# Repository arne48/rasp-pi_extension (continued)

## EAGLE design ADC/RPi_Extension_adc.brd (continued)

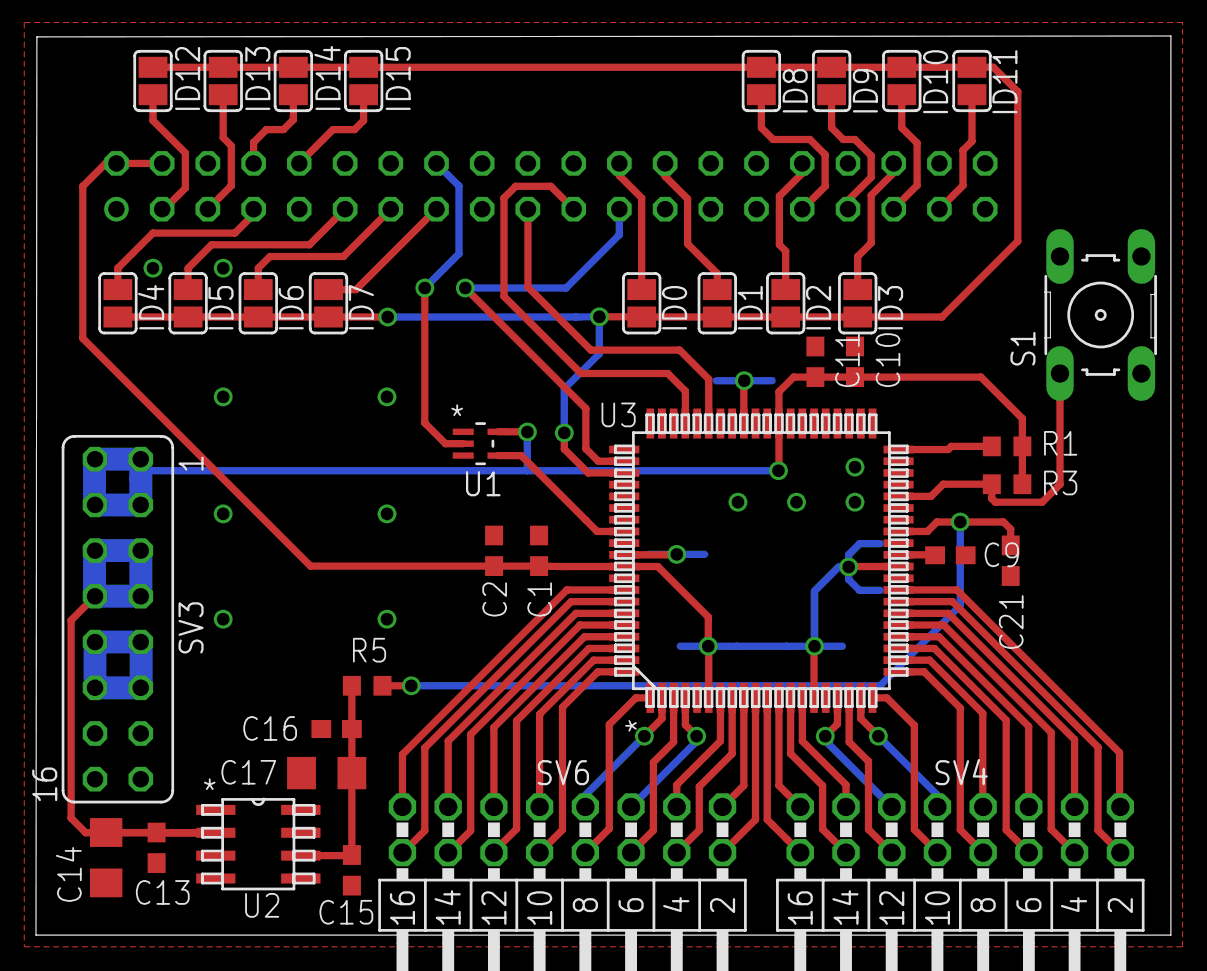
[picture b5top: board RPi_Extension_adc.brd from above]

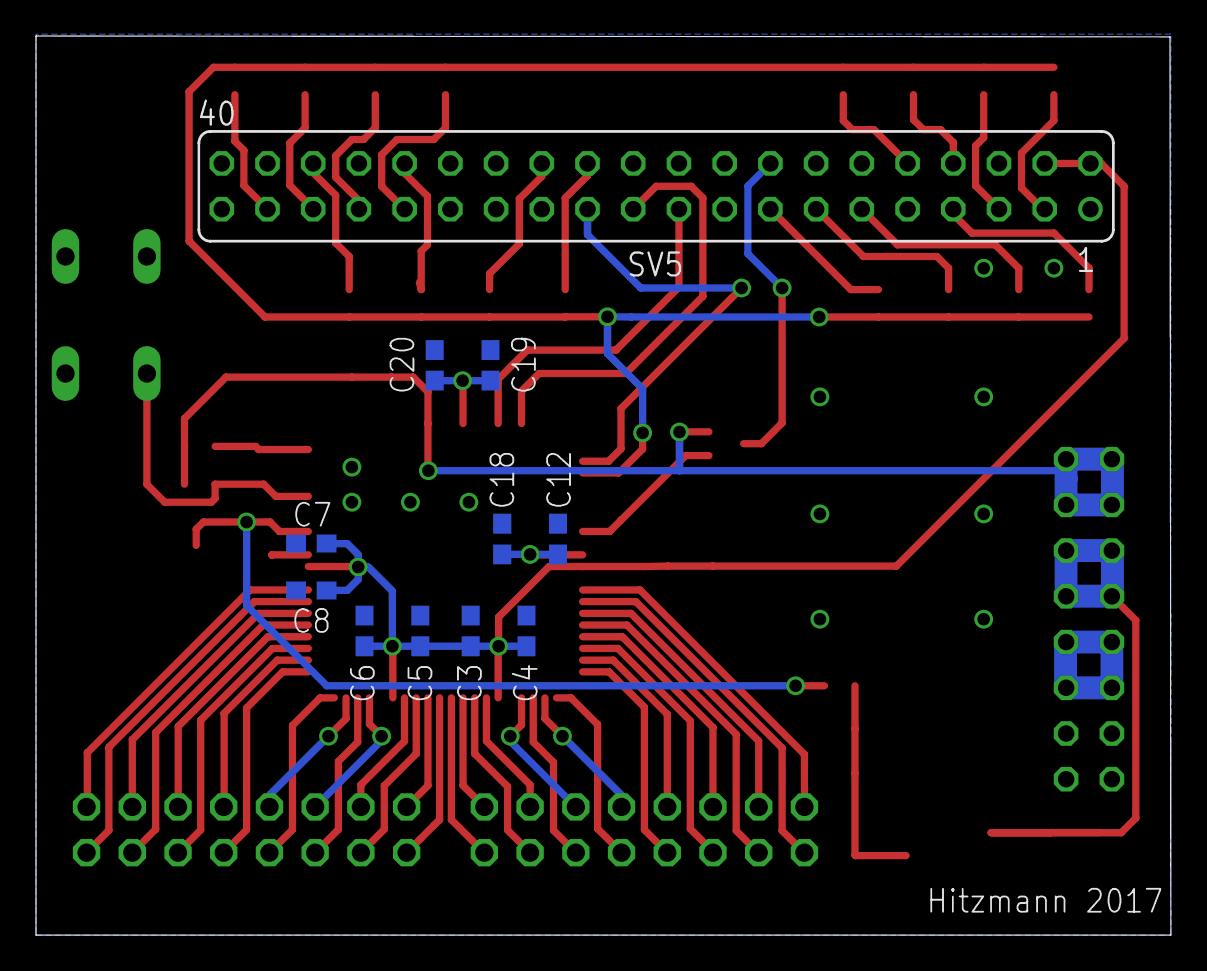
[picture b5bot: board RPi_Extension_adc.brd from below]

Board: 2 copper layers, 63.0 x 50.0 mm, 48 parts (11 on the bottom side), 66 nets.

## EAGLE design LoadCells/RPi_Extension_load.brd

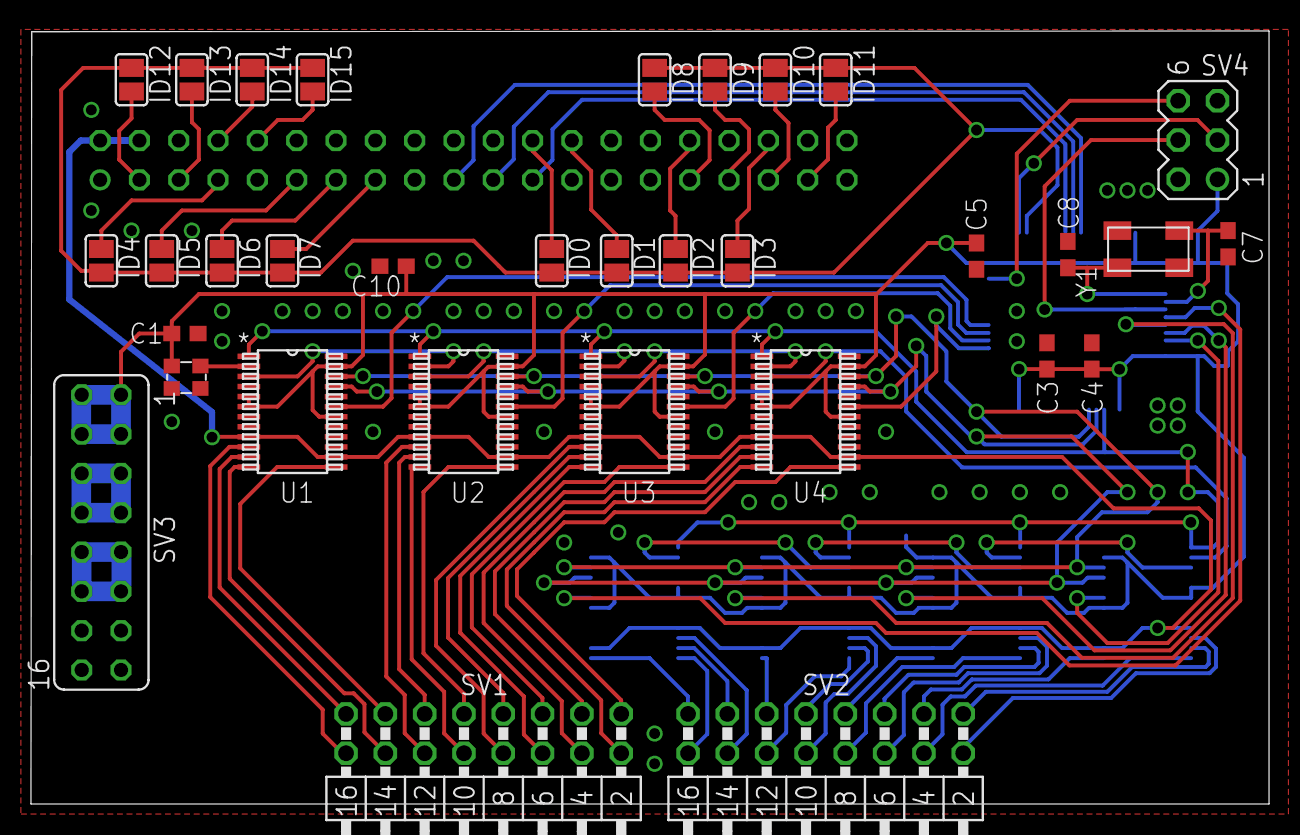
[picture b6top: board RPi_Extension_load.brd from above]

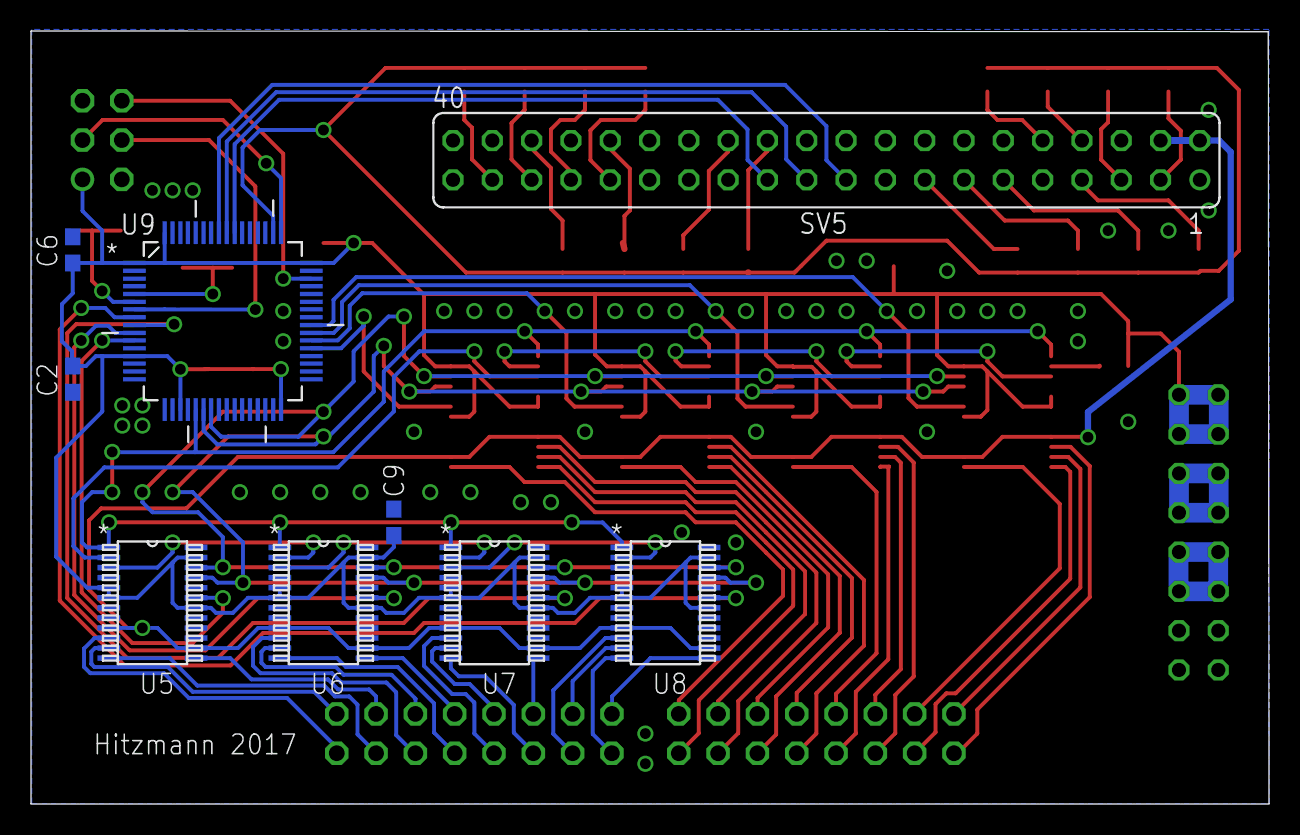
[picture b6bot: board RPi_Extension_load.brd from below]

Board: 2 copper layers, 80.0 x 50.0 mm, 42 parts (9 on the bottom side), 81 nets.

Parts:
C1, C2, C3, C4, C5, C6, C9, C10: 100nF; C0603
C7, C8: 33pf; C0603
ID0, ID1, ID2, ID3, ID4, ID5, ID6, ID7, ID8, ID9, ID10, ID11, ID12, ID13, ID14, ID15: SJ
SV1, SV2: MA08-2W
SV3: FE08-2
SV4: MA03-2
SV5: FE20-2
U1, U2, U3, U4, U5, U6, U7, U8: AD7730BRUZ; RU_24
U9: STM32F103RCT6; QFP50P1200X1200X160-64N
Y1: ABM3B
Y2: KC2520B-C1

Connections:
+5V: SV5.2, SV5.4, U1.9, U1.14, U2.9, U2.14, U3.9, U3.14, U4.9, U4.14, U5.9, U5.14, U6.9, U6.14, U7.9, U7.14, U8.9, U8.14
DVCC: C1.2, C2.2, C3.1, C4.1, C5.1, C6.1, C9.1, C10.1, SV3.1, SV3.2, SV3.3, SV3.4, SV4.1, U1.5, U1.6, U1.18, U1.23, U2.5, U2.6, U2.18, U2.23, U3.5, U3.6, U3.18, U3.23, U4.5, U4.6, U4.18, U4.23, U5.5, U5.6, U5.18, U5.23, U6.5, U6.6, U6.18, U6.23, U7.5, U7.6, U7.18, U7.23, U8.5, U8.6, U8.18, U8.23, U9.1, U9.13, U9.19, U9.32, U9.48, U9.64, Y2.4
GND: C1.1, C2.1, C3.2, C4.2, C5.2, C6.2, C7.2, C8.2, C9.2, C10.2, SV3.13, SV3.14, SV3.15, SV3.16, SV4.2, SV4.5, SV5.6, SV5.9, SV5.14, SV5.20, SV5.25, SV5.30, SV5.34, SV5.39, U1.4, U1.8, U1.15, U1.24, U2.4, U2.8, U2.15, U2.24, U3.4, U3.8, U3.15, U3.24, U4.4, U4.8, U4.15, U4.24, U5.4, U5.8, U5.15, U5.24, U6.4, U6.8, U6.15, U6.24, U7.4, U7.8, U7.15, U7.24, U8.4, U8.8, U8.15, U8.24, U9.12, U9.18, U9.31, U9.47, U9.63, Y1.2, Y1.4, Y2.2
MCLK: U1.2, Y2.3
MISO: SV5.21, U9.56
MOSI: SV5.19, U9.57
unnamed: ID11.1, SV5.37
unnamed: C8.1, U9.5, Y1.1
unnamed: C7.1, U9.6, Y1.3
unnamed: ID10.1, SV5.35
unnamed: ID9.1, SV5.33
unnamed: ID8.1, SV5.31
unnamed: ID14.1, SV5.8
unnamed: ID15.1, SV5.10
unnamed: ID12.1, SV5.3
unnamed: ID13.1, SV5.5
unnamed: ID3.1, SV5.36
unnamed: ID4.1, SV5.7
unnamed: ID2.1, SV5.32
unnamed: ID1.1, SV5.26
unnamed: ID0.1, SV5.24
unnamed: ID5.1, SV5.11
unnamed: ID6.1, SV5.13
unnamed: ID7.1, SV5.15
NRST: SV4.4, U9.7
SCLK: SV5.23, U9.55
SPI1_MISO: U1.21, U2.21, U3.21, U4.21, U5.21, U6.21, U7.21, U8.21, U9.22
SPI1_MOSI: U1.22, U2.22, U3.22, U4.22, U5.22, U6.22, U7.22, U8.22, U9.23
SPI1_SCK: U1.1, U2.1, U3.1, U4.1, U5.1, U6.1, U7.1, U8.1, U9.21
SS1: U1.19, U9.40
SS2: U2.19, U9.39
SS3: U3.19, U9.38
SS4: U4.19, U9.37
SS5: U5.19, U9.11
SS6: U6.19, U9.10
SS7: U7.19, U9.9
SS8: U8.19, U9.8
SS_STACK: ID0.2, ID1.2, ID2.2, ID3.2, ID4.2, ID5.2, ID6.2, ID7.2, ID8.2, ID9.2, ID10.2, ID11.2, ID12.2, ID13.2, ID14.2, ID15.2, U9.50
SWDCLK: SV4.3, U9.49
SWDIO: SV4.6, U9.46
U1_AIN1_+: SV1.16, U1.10
U1_AIN1_-: SV1.15, U1.11
U1_AIN2_+: SV1.14, U1.12
U1_AIN2_-: SV1.13, U1.13
U1_MCLK_OUT: U1.3, U2.2
U2_AIN1_+: SV1.12, U2.10
U2_AIN1_-: SV1.11, U2.11
U2_AIN2_+: SV1.10, U2.12
U2_AIN2_-: SV1.9, U2.13
U2_MCLK_OUT: U2.3, U3.2
U3_AIN1_+: SV1.8, U3.10
U3_AIN1_-: SV1.7, U3.11
U3_AIN2_+: SV1.6, U3.12
U3_AIN2_-: SV1.5, U3.13
U3_MCLK_OUT: U3.3, U4.2
U4_AIN1_+: SV1.4, U4.10
U4_AIN1_-: SV1.3, U4.11
U4_AIN2_+: SV1.2, U4.12
U4_AIN2_-: SV1.1, U4.13
U4_MCLK_OUT: U4.3, U5.2
U5_AIN1_+: SV2.2, U5.10
U5_AIN1_-: SV2.1, U5.11
U5_AIN2_+: SV2.4, U5.12
U5_AIN2_-: SV2.3, U5.13
U5_MCLK_OUT: U5.3, U6.2
U6_AIN1_+: SV2.6, U6.10
U6_AIN1_-: SV2.5, U6.11
U6_AIN2_+: SV2.8, U6.12
U6_AIN2_-: SV2.7, U6.13
U6_MCLK_OUT: U6.3, U7.2
U7_AIN1_+: SV2.10, U7.10
U7_AIN1_-: SV2.9, U7.11
U7_AIN2_+: SV2.12, U7.12
U7_AIN2_-: SV2.11, U7.13
U7_MCLK_OUT: U7.3, U8.2
U8_AIN1_+: SV2.14, U8.10
U8_AIN1_-: SV2.13, U8.11
U8_AIN2_+: SV2.16, U8.12
U8_AIN2_-: SV2.15, U8.13
VDD: SV3.5, SV3.6, SV3.7, SV3.8
VSS: SV3.9, SV3.10, SV3.11, SV3.12

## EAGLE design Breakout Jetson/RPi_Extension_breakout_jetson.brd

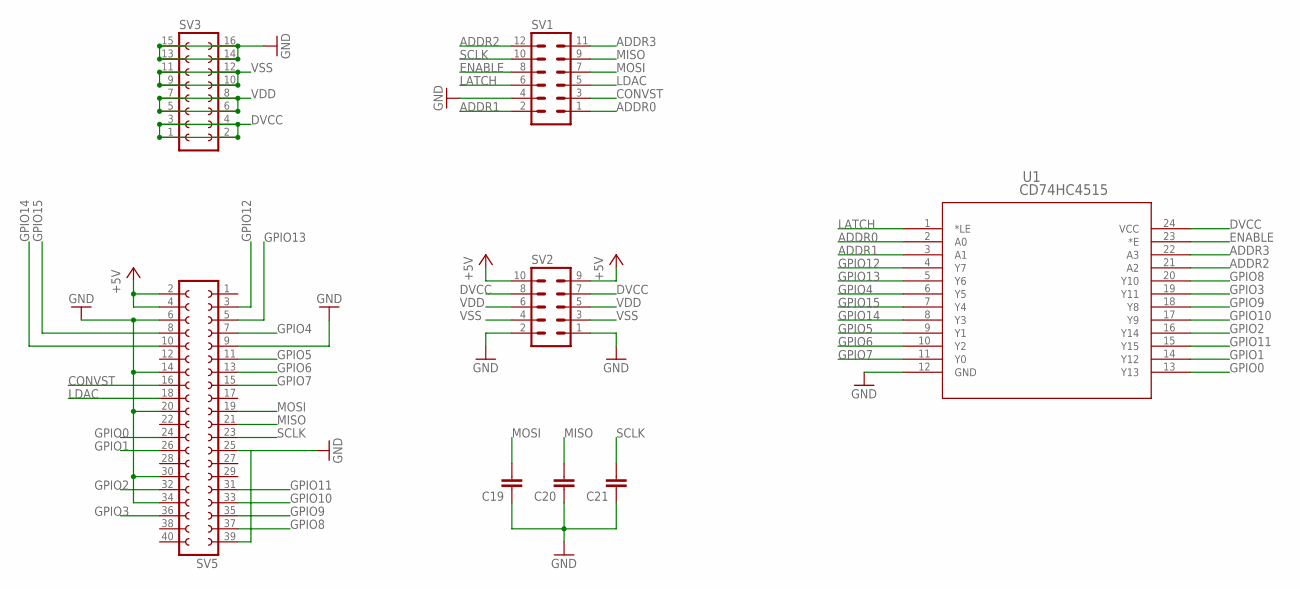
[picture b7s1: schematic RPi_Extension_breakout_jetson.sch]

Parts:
C19, C20, C21: C-EUC0603; C0603
SV1: MA06-2
SV2: MA05-2
SV3: FE08-2
SV5: FE20-2
U1: CD74HC4515; DW24

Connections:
+5V: SV2.9, SV2.10, SV5.2, SV5.4
ADDR0: SV1.1, U1.2 (A0)
ADDR1: SV1.2, U1.3 (A1)
ADDR2: SV1.12, U1.21 (A2)
ADDR3: SV1.11, U1.22 (A3)
CONVST: SV1.3, SV5.16
DVCC: SV2.7, SV2.8, SV3.1, SV3.2, SV3.3, SV3.4, U1.24 (VCC)
ENABLE: SV1.8, U1.23 (*E)
GND: C19.1, C20.1, C21.1, SV1.4, SV2.1, SV2.2, SV3.13, SV3.14, SV3.15, SV3.16, SV5.6, SV5.9, SV5.14, SV5.20, SV5.25, SV5.30, SV5.34, SV5.39, U1.12 (GND)
GPIO0: SV5.24, U1.13 (Y13)
GPIO1: SV5.26, U1.14 (Y12)
GPIO2: SV5.32, U1.16 (Y14)
GPIO3: SV5.36, U1.19 (Y11)
GPIO4: SV5.7, U1.6 (Y5)
GPIO5: SV5.11, U1.9 (Y1)
GPIO6: SV5.13, U1.10 (Y2)
GPIO7: SV5.15, U1.11 (Y0)
GPIO8: SV5.37, U1.20 (Y10)
GPIO9: SV5.35, U1.18 (Y8)
GPIO10: SV5.33, U1.17 (Y9)
GPIO11: SV5.31, U1.15 (Y15)
GPIO12: SV5.3, U1.4 (Y7)
GPIO13: SV5.5, U1.5 (Y6)
GPIO14: SV5.10, U1.8 (Y3)
GPIO15: SV5.8, U1.7 (Y4)
LATCH: SV1.6, U1.1 (*LE)
LDAC: SV1.5, SV5.18
MISO: C20.2, SV1.9, SV5.21
MOSI: C19.2, SV1.7, SV5.19
SCLK: C21.2, SV1.10, SV5.23
VDD: SV2.5, SV2.6, SV3.5, SV3.6, SV3.7, SV3.8
VSS: SV2.3, SV2.4, SV3.9, SV3.10, SV3.11, SV3.12

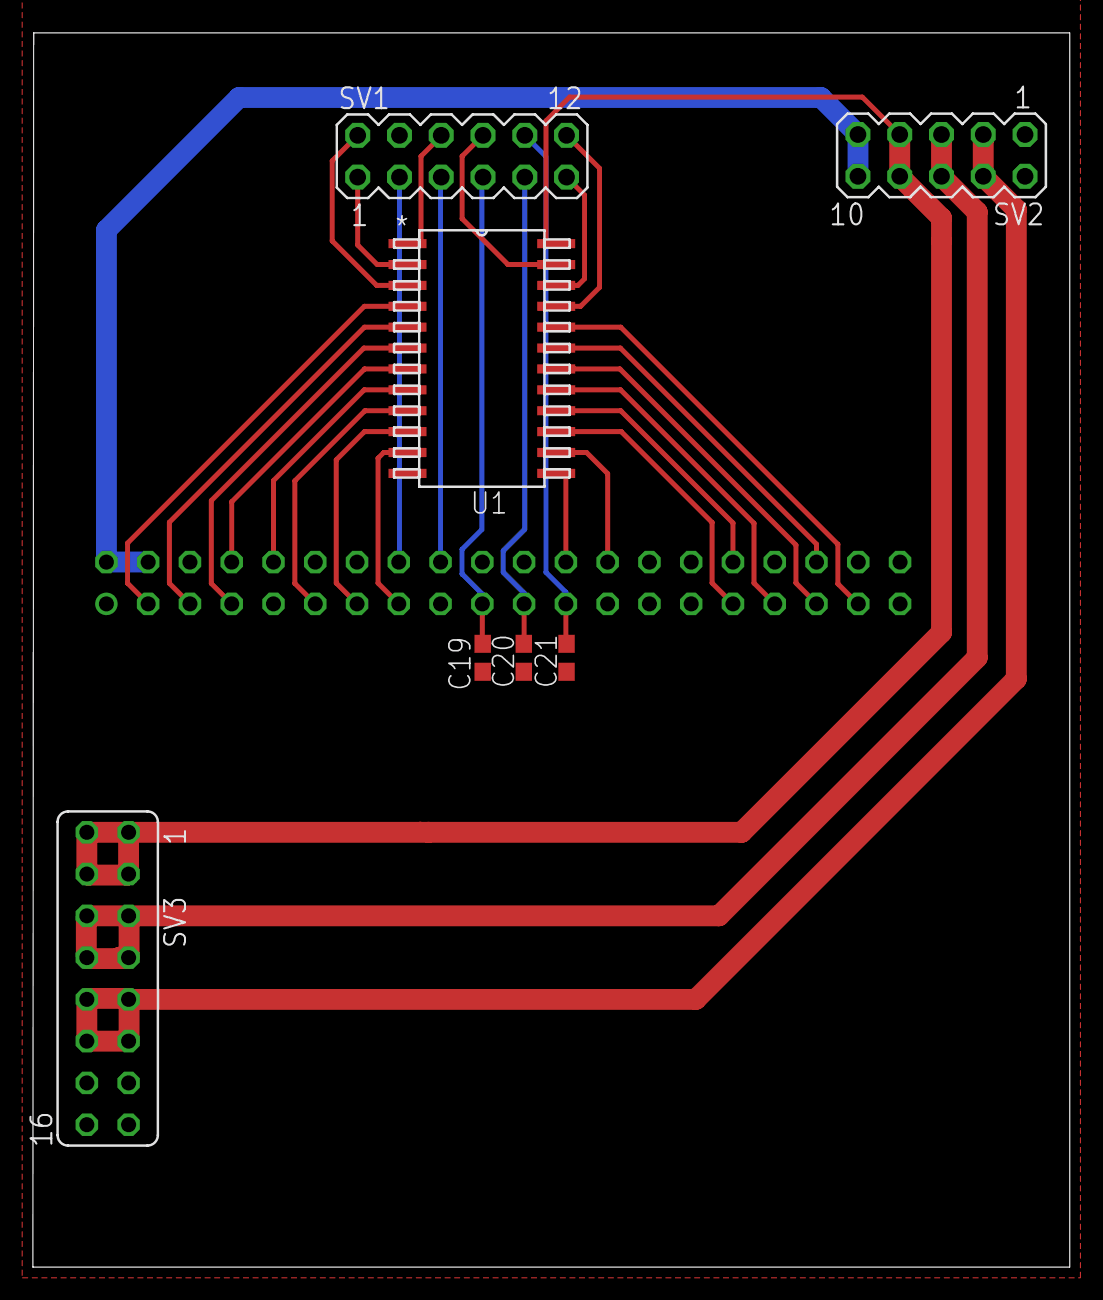
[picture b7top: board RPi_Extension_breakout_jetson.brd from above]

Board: 2 copper layers, 63.0 x 75.0 mm, 8 parts (1 on the bottom side), 32 nets.

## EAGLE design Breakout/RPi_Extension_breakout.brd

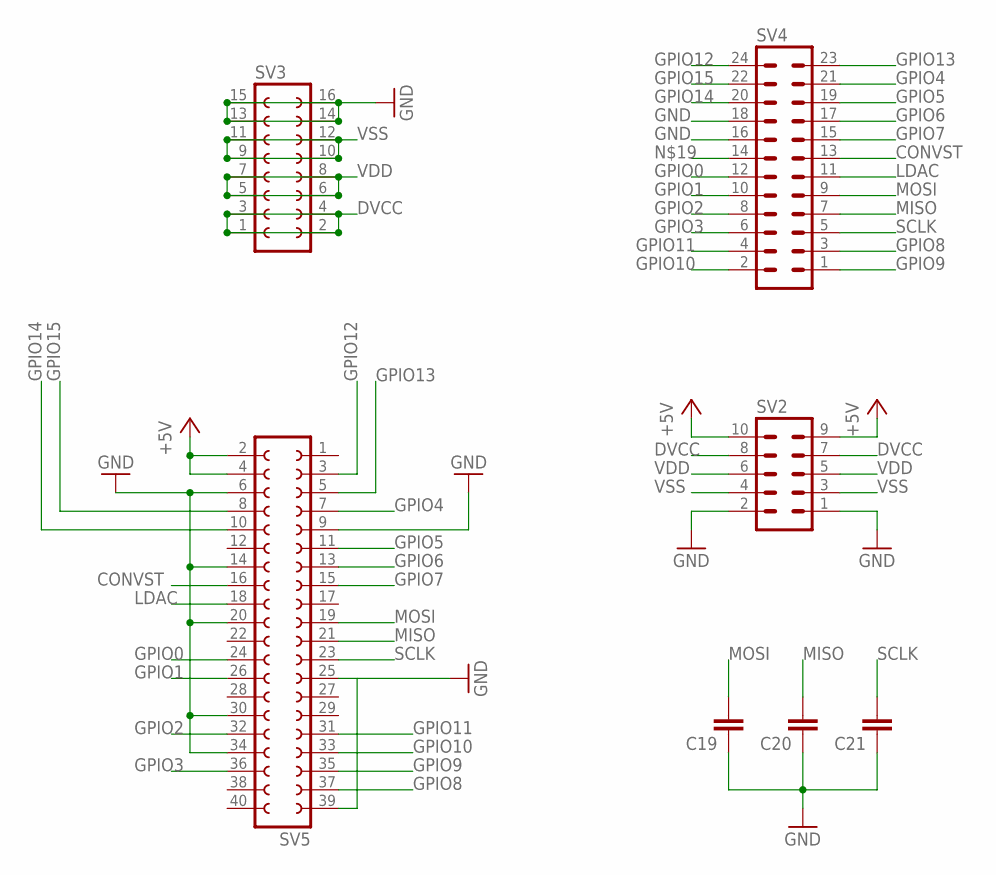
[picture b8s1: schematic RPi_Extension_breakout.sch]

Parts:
C19, C20, C21: C-EUC0603; C0603
SV2: MA05-2
SV3: FE08-2
SV4: MA12-2
SV5: FE20-2

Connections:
+5V: SV2.9, SV2.10, SV5.2, SV5.4
CONVST: SV4.13, SV5.16
DVCC: SV2.7, SV2.8, SV3.1, SV3.2, SV3.3, SV3.4
GND: C19.1, C20.1, C21.1, SV2.1, SV2.2, SV3.13, SV3.14, SV3.15, SV3.16, SV4.16, SV4.18, SV5.6, SV5.9, SV5.14, SV5.20, SV5.25, SV5.30, SV5.34, SV5.39
GPIO0: SV4.12, SV5.24
GPIO1: SV4.10, SV5.26
GPIO2: SV4.8, SV5.32
GPIO3: SV4.6, SV5.36
GPIO4: SV4.21, SV5.7
GPIO5: SV4.19, SV5.11
GPIO6: SV4.17, SV5.13
GPIO7: SV4.15, SV5.15
GPIO8: SV4.3, SV5.37
GPIO9: SV4.1, SV5.35
GPIO10: SV4.2, SV5.33
GPIO11: SV4.4, SV5.31
GPIO12: SV4.24, SV5.3
GPIO13: SV4.23, SV5.5
GPIO14: SV4.20, SV5.10
GPIO15: SV4.22, SV5.8
LDAC: SV4.11, SV5.18
MISO: C20.2, SV4.7, SV5.21
MOSI: C19.2, SV4.9, SV5.19
SCLK: C21.2, SV4.5, SV5.23
VDD: SV2.5, SV2.6, SV3.5, SV3.6, SV3.7, SV3.8
VSS: SV2.3, SV2.4, SV3.9, SV3.10, SV3.11, SV3.12

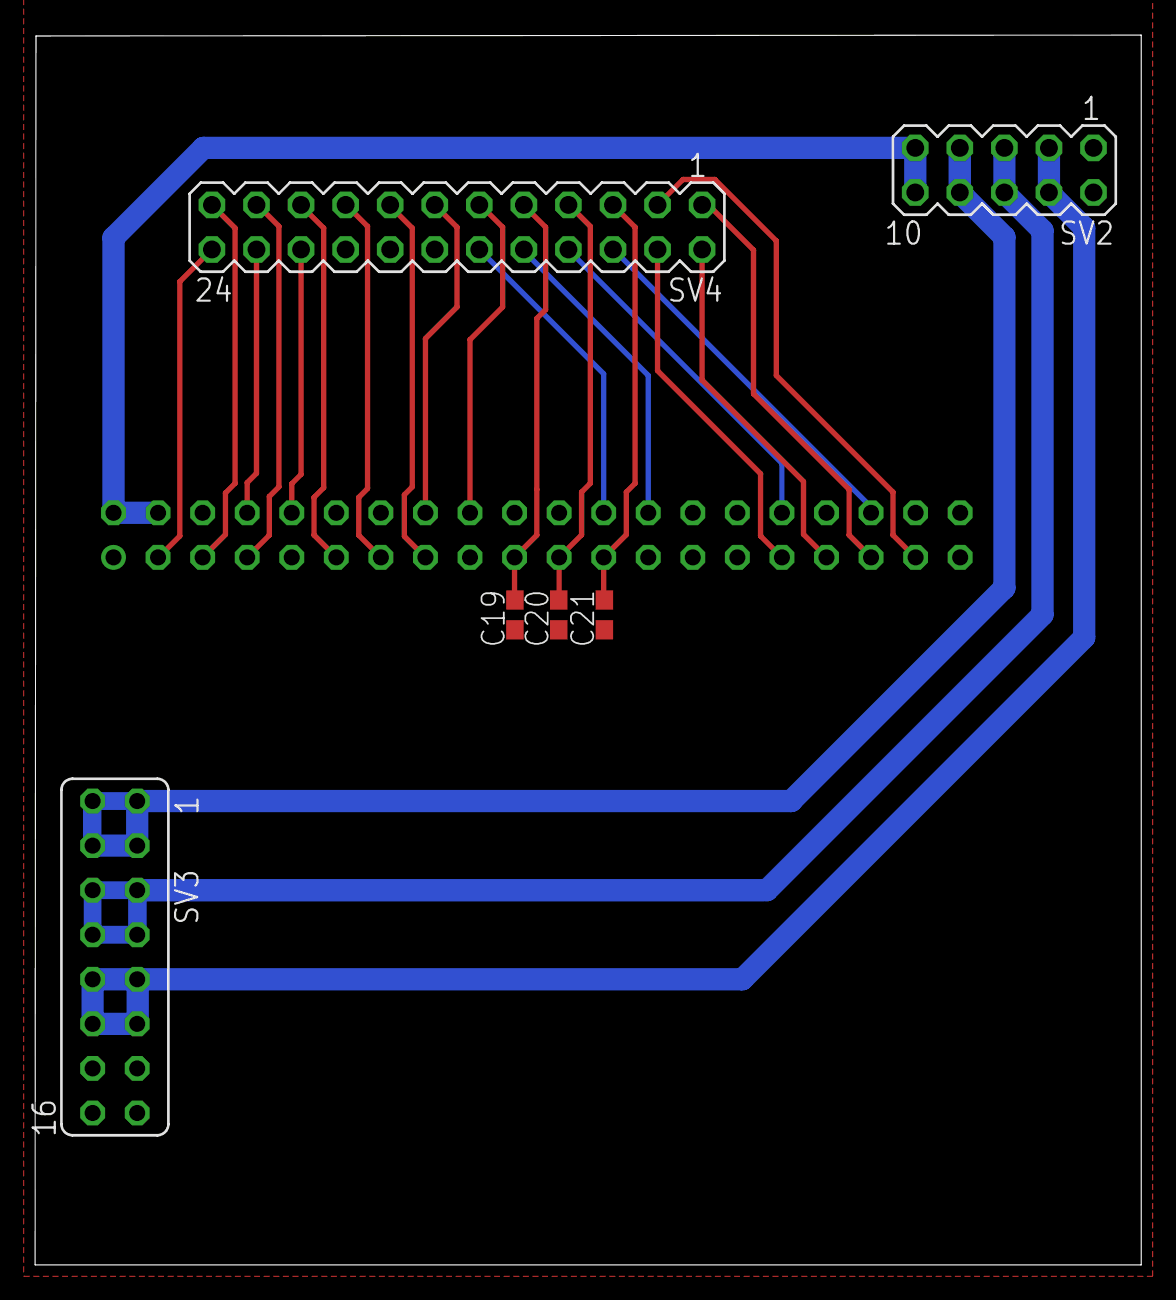
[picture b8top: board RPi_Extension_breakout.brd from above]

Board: 2 copper layers, 63.0 x 70.1 mm, 7 parts (1 on the bottom side), 26 nets.

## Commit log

2016-11-30 updated structure and designs
2016-12-01 updated scale board
2016-12-02 finished top layer of scale board
2016-12-02 added small design improvements
2016-12-03 updated design
2016-12-04 added second set of transducers
2016-12-05 shifted top ics and rerouted some signals for compliance
2016-12-05 added traces to load cell connectors
2016-12-05 fixed grounding error and missplaced trace
2016-12-05 added crystal and revisited layout
2016-12-05 vias revisited
2016-12-21 updated pcbs
2017-01-06 added address lines up to 16 to loadcell board
2017-01-10 created gerber files for adc and load cell board and did some retouch on load cell board
2017-01-13 reworked PSU layout
2017-01-13 renamed weightcells to loadcells
2017-01-13 retouched load cell board
2017-01-13 used consistent naming and units for values
2017-01-13 added additional id jumpers to adc and dac board
2017-01-16 added multiplexed breakout board for jetson tx1
2017-01-17 added additional jetson breakout board just using one 1:16 multiplexer
2017-01-17 updated package of 1:16 multiplexer
2017-01-18 added inverters to jetson tx1 board
2017-01-18 made pads of multiplexer square and started to solve remaining drc errors
2017-01-19 rearranged pins on jetson board for a nicer layout
2017-01-19 fixed drc errors on jetson tx1 board
2017-01-19 fixed minor drc error in dac board
2017-01-19 changed used component to one 1 to 16 multiplexer on basic jetson tx1 board
2017-01-23 cleaned up silklayer of psu board
2017-01-23 cleaned up silklayer of dac board
2017-01-23 cleaned up silklayer of load cell board
2017-01-23 cleaned up silklayer of breakout boards
2017-01-25 added more documentation
2017-01-27 changed minor details
2017-02-06 added additional loadcell design using ready signals
2017-02-06 completed additional loadcell design using ready signals
2017-02-10 fixed severe bug on adc board
2017-02-10 added designer reference to adc board
2017-02-11 small relocations of decoupling caps on adc board
2017-02-15 minor rerouting to remove useless corners
2017-02-20 started design of connector board
2017-02-20 added 40pin connector using 3pin 2row for each muscle
2017-02-20 finished first half of connector board
2017-02-21 finished second half of connector board
2017-02-21 adjusted silkscreen
2017-02-21 got more isolation
2017-02-21 changed dac header to 34pin
2017-02-22 changed traces of adc connectors to proper size according to their pads
2017-02-24 closed schematic in eagle project file
2017-03-02 small changes
2017-03-02 using jst-ph connectors instead of molex micro blade
2017-03-06 added additional ground vias
2017-03-23 added controller pinouts
2017-03-24 disconnected shorting ground connection on connector board
2017-04-03 updated content before making repository public
2017-12-05 updated reference voltage on dac board
2018-01-30 added additional parts
2018-01-30 added RPi power supply
2018-02-05 added fan and leds
2018-02-15 now using polarized symbol for tantalum caps
2018-02-20 added vertical connector to power board
2018-04-13 increased isolation of traces
2018-04-13 minor changes
